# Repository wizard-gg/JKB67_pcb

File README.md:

# JKB67 RGB

[![CC BY-NC-SA 4.0][cc-by-nc-sa-shield]][cc-by-nc-sa]

## JKB65 RGB Hotswap PCB, compatible [Bakeneko65 V3](https://github.com/kkatano/bakeneko-65) Keyboard

---

## Front

## Back

---

[KiCAD PCB files](pcb/)

[Gerbers for PCB production](pcb/gerber/)

[QMK firmware](https://github.com/qmk/qmk_firmware/tree/master/keyboards/jadookb/jkb65)

[Fr4 Plate](https://github.com/desuko-mirai/Bakeneko-Screw-In-Stabilizer-Plates)

---

This work is licensed under a
[Creative Commons Attribution-NonCommercial-ShareAlike 4.0 International License][cc-by-nc-sa].

[![CC BY-NC-SA 4.0][cc-by-nc-sa-image]][cc-by-nc-sa]

[cc-by-nc-sa]: http://creativecommons.org/licenses/by-nc-sa/4.0/
[cc-by-nc-sa-image]: https://licensebuttons.net/l/by-nc-sa/4.0/88x31.png
[cc-by-nc-sa-shield]: https://img.shields.io/badge/License-CC%20BY--NC--SA%204.0-lightgrey.svg

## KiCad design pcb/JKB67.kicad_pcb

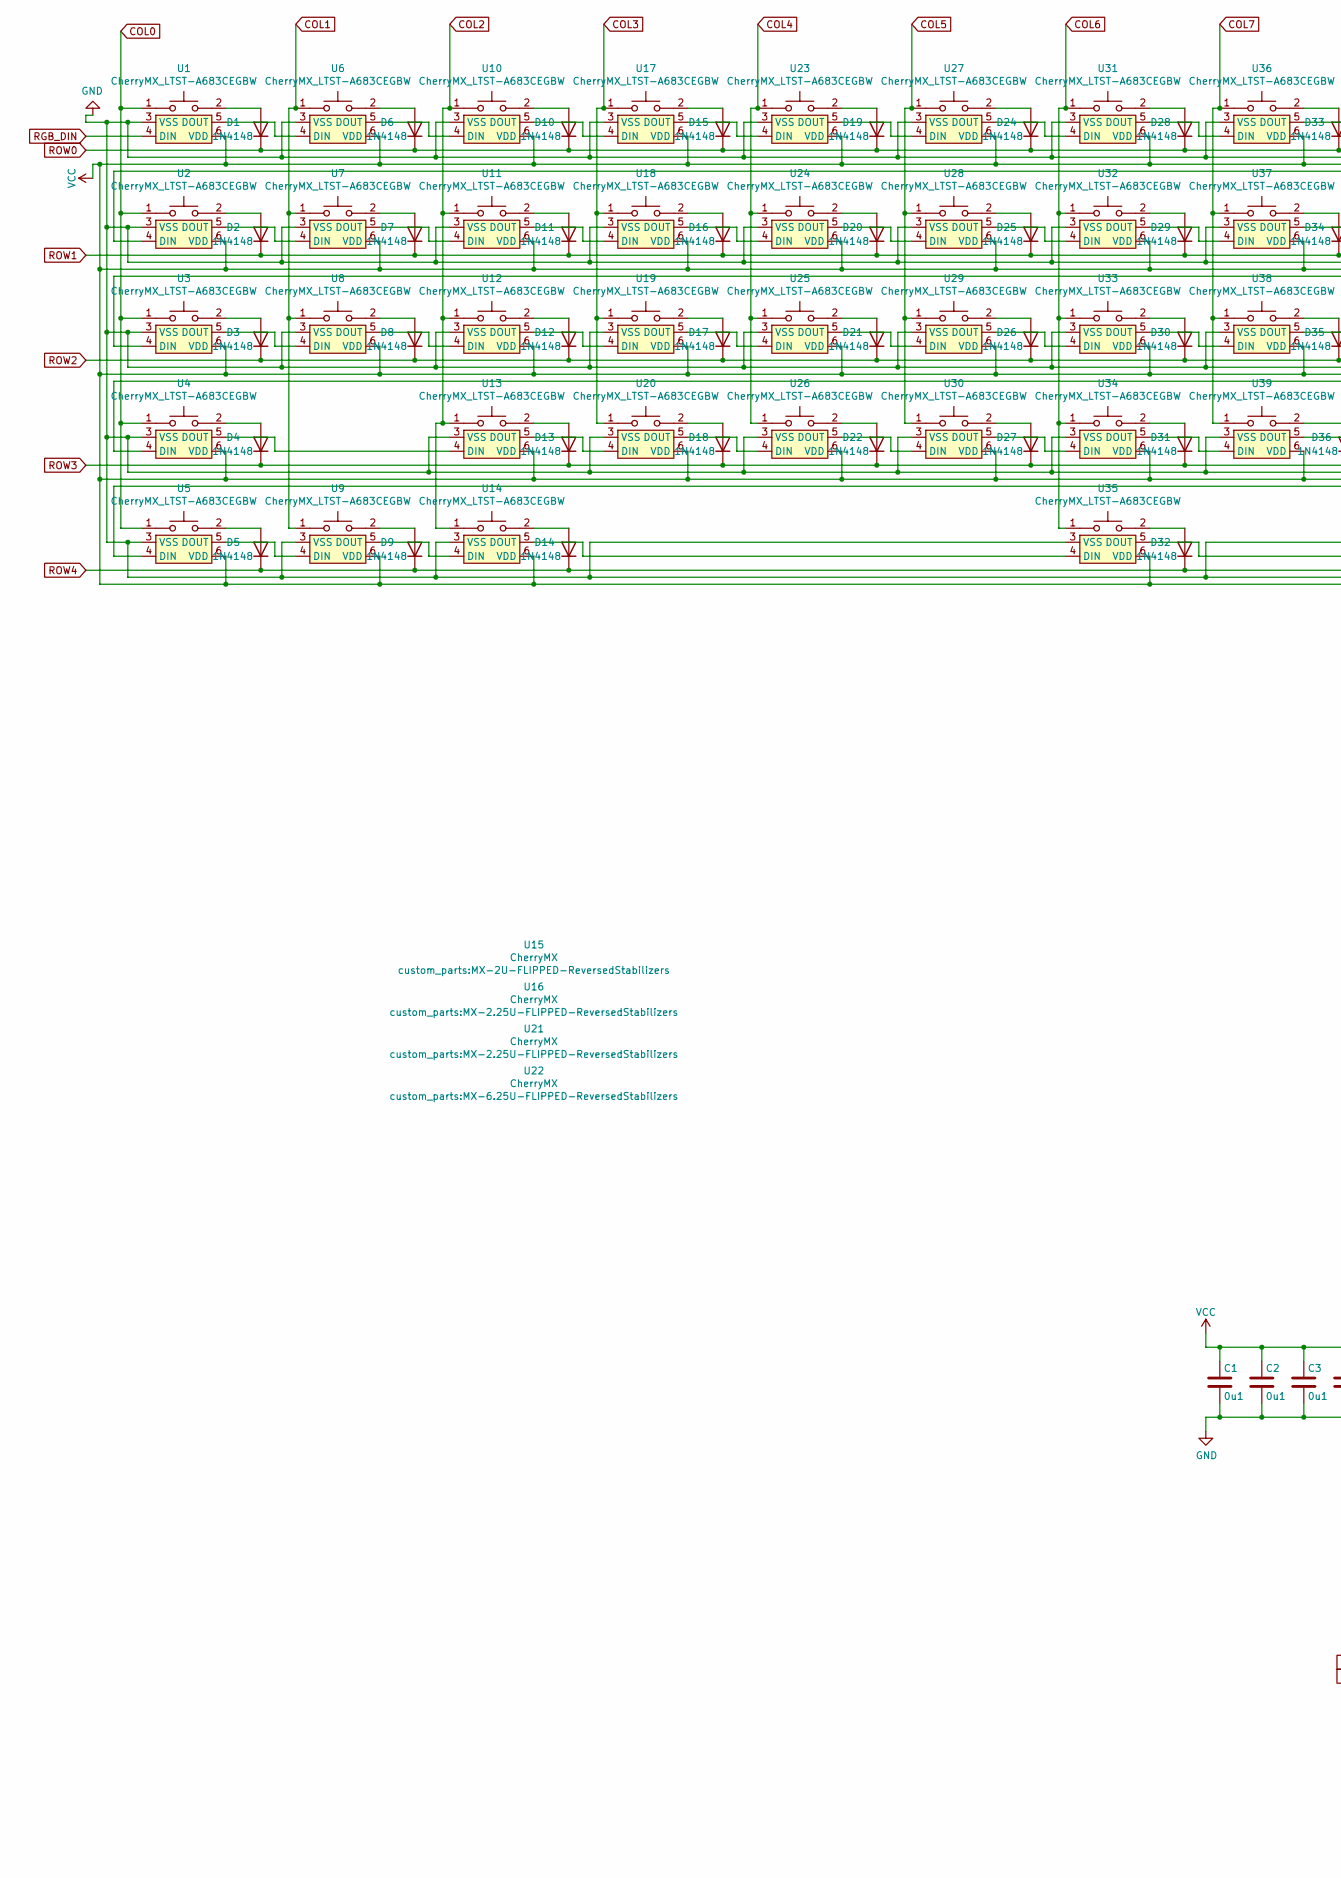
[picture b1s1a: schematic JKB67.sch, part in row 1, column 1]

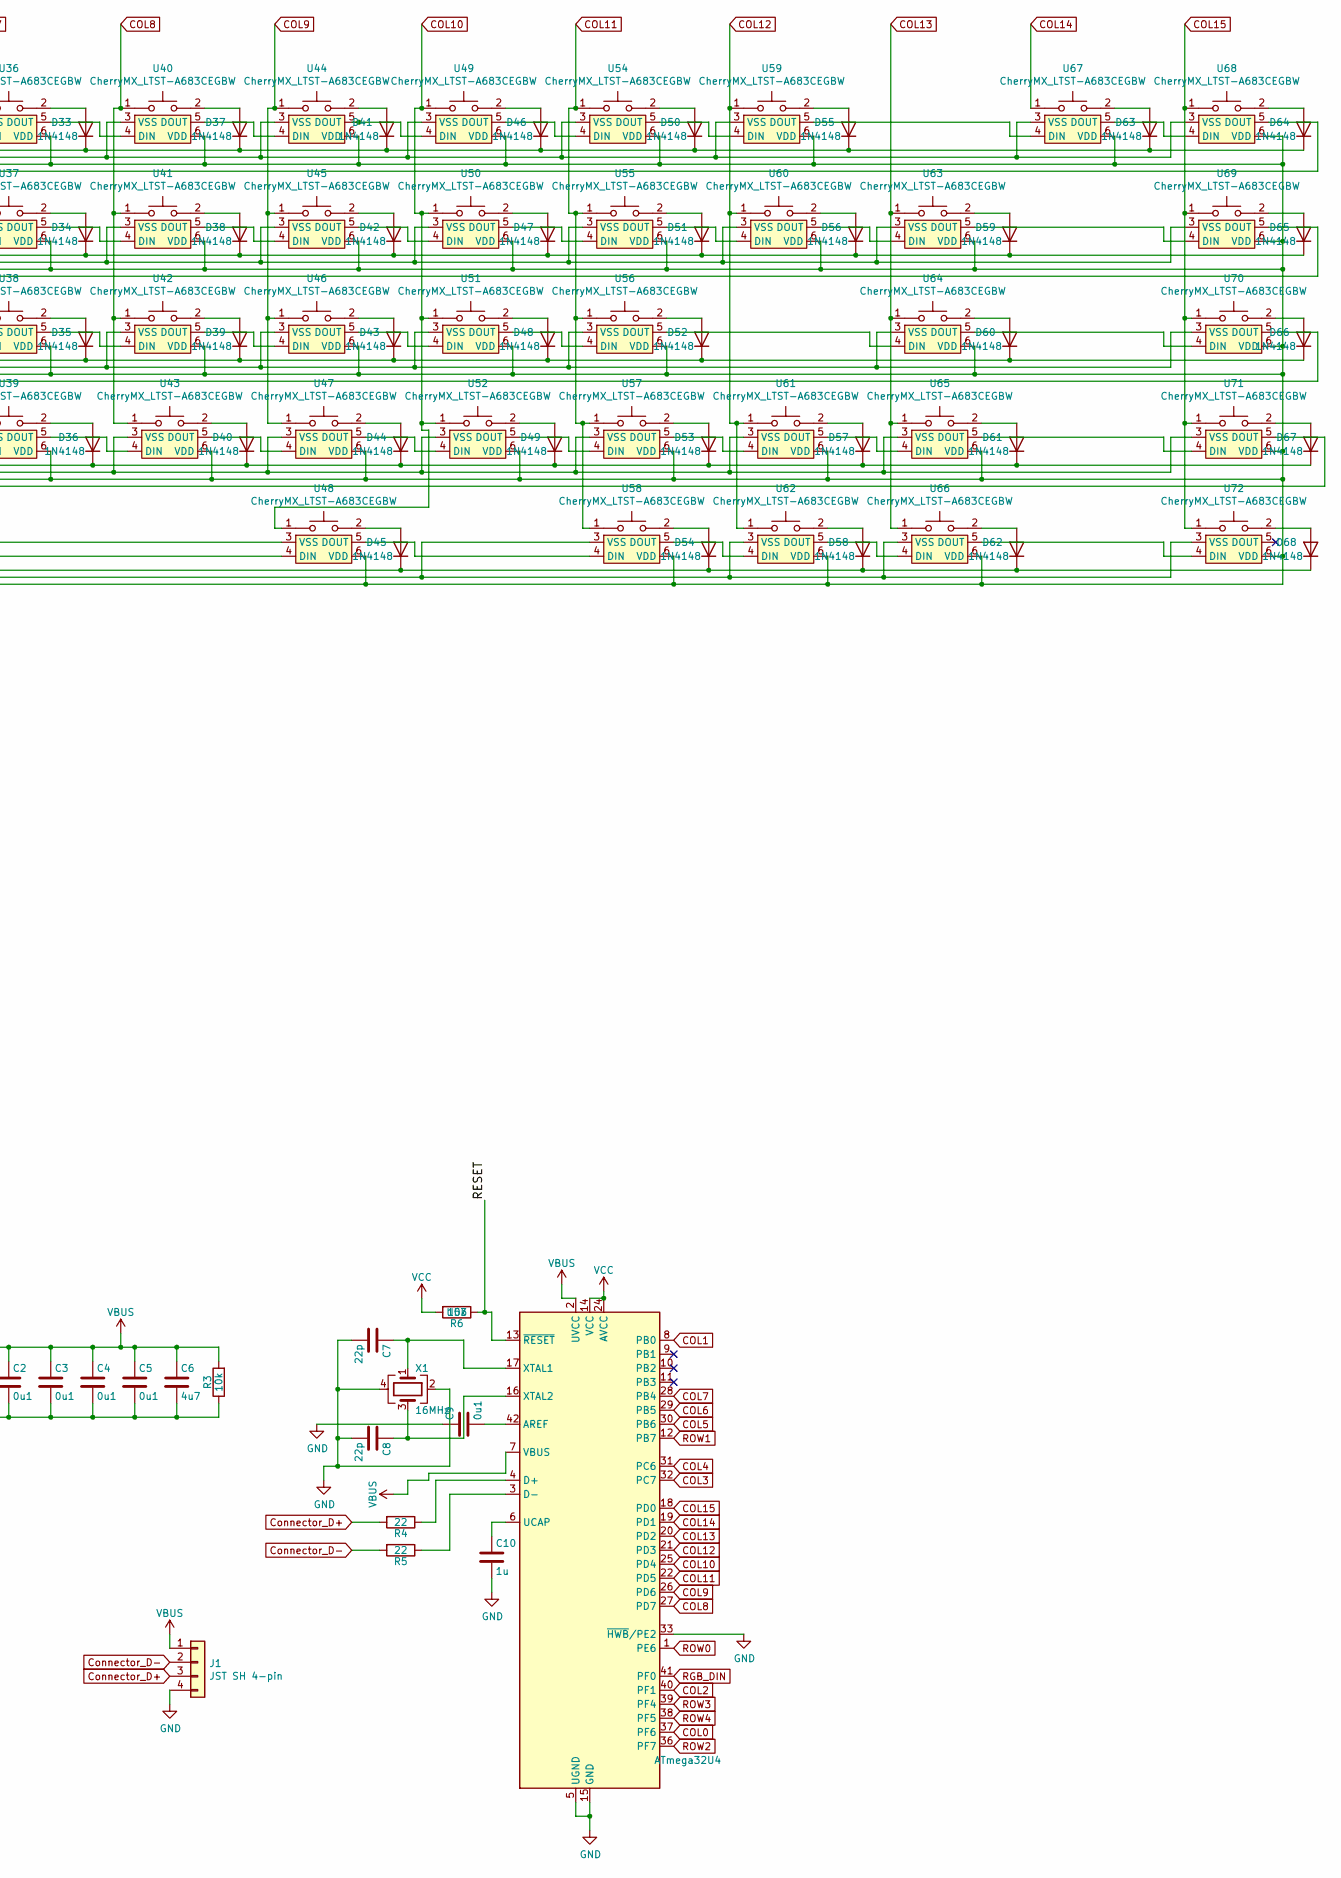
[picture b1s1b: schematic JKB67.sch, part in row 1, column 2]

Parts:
C1, C2, C3, C4, C5, C9: 0u1; C_0805_2012Metric_Pad1.18x1.45mm_HandSolder
C6: 4u7; C_0805_2012Metric_Pad1.18x1.45mm_HandSolder
C7, C8: 22p; C_0805_2012Metric_Pad1.18x1.45mm_HandSolder
C10: 1u; C_0805_2012Metric_Pad1.18x1.45mm_HandSolder
D1, D2, D3, D4, D5, D6, D7, D8, D9, D10, D11, D12, D13, D14, D15, D16, D17, D18, D19, D20, D21, D22, D24, D25, D26, D27, D28, D29, D30, D31, D32, D33, D34, D35, D36, D37, D38, D39, D40, D41, D42, D43, D44, D45, D46, D47, D48, D49, D50, D51, D52, D53, D54, D55, D56, D57, D58, D59, D60, D61, D62, D63, D64, D65, D66, D67, D68: 1N4148; D_SOD-123F; LCSC Part # C81598
J1: JST SH 4-pin; JST_SH_SM04B-SRSS-TB_04x1.25mm
R3, R6: 10k; R_0805_2012Metric_Pad1.20x1.40mm_HandSolder
R4, R5: 22; R_0805_2012Metric_Pad1.20x1.40mm_HandSolder
U1, U6, U7, U8, U10, U11, U12, U13, U17, U18, U19, U20, U23, U24, U25, U26, U27, U28, U29, U30, U31, U32, U33, U34, U36, U37, U38, U39, U40, U41, U42, U43, U44, U45, U46, U47, U49, U50, U51, U52, U54, U55, U56, U57, U59, U60, U62, U65, U66, U68, U69, U70, U71, U72: CherryMX_LTST-A683CEGBW; CherryMX_1.00u_5Pin_SK6812Mini
U2, U63: CherryMX_LTST-A683CEGBW; CherryMX_1.50u_5Pin_SK6812Mini
U3, U61: CherryMX_LTST-A683CEGBW; CherryMX_1.75u_5Pin_SK6812Mini
U4, U64: CherryMX_LTST-A683CEGBW; CherryMX_2.25u_5Pin_SK6812Mini
U5, U9, U14, U48, U58: CherryMX_LTST-A683CEGBW; CherryMX_1.25u_5Pin_SK6812Mini
U15: CherryMX; MX-2U-FLIPPED-ReversedStabilizers
U16, U21: CherryMX; MX-2.25U-FLIPPED-ReversedStabilizers
U22: CherryMX; MX-6.25U-FLIPPED-ReversedStabilizers
U35: CherryMX_LTST-A683CEGBW; CherryMX_6.25u_5Pin_SK6812Mini
U53: ATmega32U4; TQFP-44_10x10mm_P0.8mm
U67: CherryMX_LTST-A683CEGBW; CherryMX_2.00u_5Pin_SK6812Mini
X1: 16MHz; Crystal_SMD_SeikoEpson_FA238-4Pin_3.2x2.5mm

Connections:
/RESET: R6.1, U53.13 (~RESET)
COL0: U1.1, U2.1, U3.1, U4.1, U5.1, U53.37 (PF6)
COL1: U6.1, U7.1, U8.1, U9.1, U53.8 (PB0)
COL2: U10.1, U11.1, U12.1, U13.1, U14.1, U53.40 (PF1)
COL3: U17.1, U18.1, U19.1, U20.1, U53.32 (PC7)
COL4: U23.1, U24.1, U25.1, U26.1, U53.31 (PC6)
COL5: U27.1, U28.1, U29.1, U30.1, U53.30 (PB6)
COL6: U31.1, U32.1, U33.1, U34.1, U35.1, U53.29 (PB5)
COL7: U36.1, U37.1, U38.1, U39.1, U53.28 (PB4)
COL8: U40.1, U41.1, U42.1, U43.1, U53.27 (PD7)
COL9: U44.1, U45.1, U46.1, U47.1, U53.26 (PD6)
COL10: U48.1, U49.1, U50.1, U51.1, U52.1, U53.25 (PD4)
COL11: U53.22 (PD5), U54.1, U55.1, U56.1, U57.1, U58.1
COL12: U53.21 (PD3), U59.1, U60.1, U61.1, U62.1
COL13: U53.20 (PD2), U63.1, U64.1, U65.1, U66.1
COL14: U53.19 (PD1), U67.1
COL15: U53.18 (PD0), U68.1, U69.1, U70.1, U71.1, U72.1
Connector_D+: J1.3, R4.2
Connector_D-: J1.2, R5.2
GND: C1.2, C2.2, C3.2, C4.2, C5.2, C6.2, C7.2, C8.2, C9.1, C10.2, J1.4, R3.1, U1.3 (VSS), U2.3 (VSS), U3.3 (VSS), U4.3 (VSS), U5.3 (VSS), U6.3 (VSS), U7.3 (VSS), U8.3 (VSS), U9.3 (VSS), U10.3 (VSS), U11.3 (VSS), U12.3 (VSS), U13.3 (VSS), U14.3 (VSS), U17.3 (VSS), U18.3 (VSS), U19.3 (VSS), U20.3 (VSS), U23.3 (VSS), U24.3 (VSS), U25.3 (VSS), U26.3 (VSS), U27.3 (VSS), U28.3 (VSS), U29.3 (VSS), U30.3 (VSS), U31.3 (VSS), U32.3 (VSS), U33.3 (VSS), U34.3 (VSS), U35.3 (VSS), U36.3 (VSS), U37.3 (VSS), U38.3 (VSS), U39.3 (VSS), U40.3 (VSS), U41.3 (VSS), U42.3 (VSS), U43.3 (VSS), U44.3 (VSS), U45.3 (VSS), U46.3 (VSS), U47.3 (VSS), U48.3 (VSS), U49.3 (VSS), U50.3 (VSS), U51.3 (VSS), U52.3 (VSS), U53.5 (UGND), U53.15 (GND), U53.23 (GND), U53.33 (~HWB~/PE2), U53.35 (GND), U53.43 (GND), U54.3 (VSS), U55.3 (VSS), U56.3 (VSS), U57.3 (VSS), U58.3 (VSS), U59.3 (VSS), U60.3 (VSS), U61.3 (VSS), U62.3 (VSS), U63.3 (VSS), U64.3 (VSS), U65.3 (VSS), U66.3 (VSS), U67.3 (VSS), U68.3 (VSS), U69.3 (VSS), U70.3 (VSS), U71.3 (VSS), U72.3 (VSS), X1.2, X1.4
unnamed: C7.1, U53.17 (XTAL1), X1.1
unnamed: C8.1, U53.16 (XTAL2), X1.3
unnamed: C9.2, U53.42 (AREF)
unnamed: C10.1, U53.6 (UCAP)
unnamed: D1.2 (A), U1.2
unnamed: D2.2 (A), U2.2
unnamed: D3.2 (A), U3.2
unnamed: D4.2 (A), U4.2
unnamed: D5.2 (A), U5.2
unnamed: D6.2 (A), U6.2
unnamed: D7.2 (A), U7.2
unnamed: D8.2 (A), U8.2
unnamed: D9.2 (A), U9.2
unnamed: D10.2 (A), U10.2
unnamed: D11.2 (A), U11.2
unnamed: D12.2 (A), U12.2
unnamed: D13.2 (A), U13.2
unnamed: D14.2 (A), U14.2
unnamed: D15.2 (A), U17.2
unnamed: D16.2 (A), U18.2
unnamed: D17.2 (A), U19.2
unnamed: D18.2 (A), U20.2
unnamed: D19.2 (A), U23.2
unnamed: D20.2 (A), U24.2
unnamed: D21.2 (A), U25.2
unnamed: D22.2 (A), U26.2
unnamed: D24.2 (A), U27.2
unnamed: D25.2 (A), U28.2
unnamed: D26.2 (A), U29.2
unnamed: D27.2 (A), U30.2
unnamed: D28.2 (A), U31.2
unnamed: D29.2 (A), U32.2
unnamed: D30.2 (A), U33.2
unnamed: D31.2 (A), U34.2
unnamed: D32.2 (A), U35.2
unnamed: D33.2 (A), U36.2
unnamed: D34.2 (A), U37.2
unnamed: D35.2 (A), U38.2
unnamed: D36.2 (A), U39.2
unnamed: D37.2 (A), U40.2
unnamed: D38.2 (A), U41.2
unnamed: D39.2 (A), U42.2
unnamed: D40.2 (A), U43.2
unnamed: D41.2 (A), U44.2
unnamed: D42.2 (A), U45.2
unnamed: D43.2 (A), U46.2
unnamed: D44.2 (A), U47.2
unnamed: D45.2 (A), U48.2
unnamed: D46.2 (A), U49.2
unnamed: D47.2 (A), U50.2
unnamed: D48.2 (A), U51.2
unnamed: D49.2 (A), U52.2
unnamed: D50.2 (A), U54.2
unnamed: D51.2 (A), U55.2
unnamed: D52.2 (A), U56.2
unnamed: D53.2 (A), U57.2
unnamed: D54.2 (A), U58.2
unnamed: D55.2 (A), U59.2
unnamed: D56.2 (A), U60.2
unnamed: D57.2 (A), U61.2
unnamed: D58.2 (A), U62.2
unnamed: D59.2 (A), U63.2
unnamed: D60.2 (A), U64.2
unnamed: D61.2 (A), U65.2
unnamed: D62.2 (A), U66.2
unnamed: D63.2 (A), U67.2
unnamed: D64.2 (A), U68.2
unnamed: D65.2 (A), U69.2
unnamed: D66.2 (A), U70.2
unnamed: D67.2 (A), U71.2
unnamed: D68.2 (A), U72.2
unnamed: R4.1, U53.4 (D+)
unnamed: R5.1, U53.3 (D-)
unnamed: U1.5 (DOUT), U6.4 (DIN)
unnamed: U2.4 (DIN), U68.5 (DOUT)
unnamed: U2.5 (DOUT), U7.4 (DIN)
unnamed: U3.4 (DIN), U69.5 (DOUT)
unnamed: U3.5 (DOUT), U8.4 (DIN)
unnamed: U4.4 (DIN), U70.5 (DOUT)
unnamed: U5.4 (DIN), U71.5 (DOUT)
unnamed: U5.5 (DOUT), U9.4 (DIN)
unnamed: U6.5 (DOUT), U10.4 (DIN)
unnamed: U10.5 (DOUT), U17.4 (DIN)
unnamed: U7.5 (DOUT), U11.4 (DIN)
unnamed: U11.5 (DOUT), U18.4 (DIN)
unnamed: U8.5 (DOUT), U12.4 (DIN)
unnamed: U12.5 (DOUT), U19.4 (DIN)
unnamed: U4.5 (DOUT), U13.4 (DIN)
unnamed: U13.5 (DOUT), U20.4 (DIN)
unnamed: U9.5 (DOUT), U14.4 (DIN)
unnamed: U14.5 (DOUT), U35.4 (DIN)
unnamed: U17.5 (DOUT), U23.4 (DIN)
unnamed: U18.5 (DOUT), U24.4 (DIN)
unnamed: U19.5 (DOUT), U25.4 (DIN)
unnamed: U20.5 (DOUT), U26.4 (DIN)
unnamed: U23.5 (DOUT), U27.4 (DIN)
unnamed: U24.5 (DOUT), U28.4 (DIN)
unnamed: U25.5 (DOUT), U29.4 (DIN)
unnamed: U26.5 (DOUT), U30.4 (DIN)
unnamed: U27.5 (DOUT), U31.4 (DIN)
unnamed: U28.5 (DOUT), U32.4 (DIN)
unnamed: U29.5 (DOUT), U33.4 (DIN)
unnamed: U30.5 (DOUT), U34.4 (DIN)
unnamed: U31.5 (DOUT), U36.4 (DIN)
unnamed: U32.5 (DOUT), U37.4 (DIN)
unnamed: U33.5 (DOUT), U38.4 (DIN)
unnamed: U34.5 (DOUT), U39.4 (DIN)
unnamed: U35.5 (DOUT), U48.4 (DIN)
unnamed: U36.5 (DOUT), U40.4 (DIN)
unnamed: U37.5 (DOUT), U41.4 (DIN)
unnamed: U38.5 (DOUT), U42.4 (DIN)
unnamed: U39.5 (DOUT), U43.4 (DIN)
unnamed: U40.5 (DOUT), U44.4 (DIN)
unnamed: U41.5 (DOUT), U45.4 (DIN)
unnamed: U42.5 (DOUT), U46.4 (DIN)
unnamed: U43.5 (DOUT), U47.4 (DIN)
unnamed: U44.5 (DOUT), U49.4 (DIN)
unnamed: U45.5 (DOUT), U50.4 (DIN)
unnamed: U46.5 (DOUT), U51.4 (DIN)
unnamed: U47.5 (DOUT), U52.4 (DIN)
unnamed: U48.5 (DOUT), U58.4 (DIN)
unnamed: U49.5 (DOUT), U54.4 (DIN)
unnamed: U50.5 (DOUT), U55.4 (DIN)
unnamed: U51.5 (DOUT), U56.4 (DIN)
unnamed: U52.5 (DOUT), U57.4 (DIN)
unnamed: U54.5 (DOUT), U59.4 (DIN)
unnamed: U55.5 (DOUT), U60.4 (DIN)
unnamed: U56.5 (DOUT), U64.4 (DIN)
unnamed: U57.5 (DOUT), U61.4 (DIN)
unnamed: U58.5 (DOUT), U62.4 (DIN)
unnamed: U59.5 (DOUT), U67.4 (DIN)
unnamed: U60.5 (DOUT), U63.4 (DIN)
unnamed: U61.5 (DOUT), U65.4 (DIN)
unnamed: U62.5 (DOUT), U66.4 (DIN)
unnamed: U63.5 (DOUT), U69.4 (DIN)
unnamed: U64.5 (DOUT), U70.4 (DIN)
unnamed: U65.5 (DOUT), U71.4 (DIN)
unnamed: U66.5 (DOUT), U72.4 (DIN)
unnamed: U67.5 (DOUT), U68.4 (DIN)
RGB_DIN: U1.4 (DIN), U53.41 (PF0)
ROW0: D1.1 (K), D6.1 (K), D10.1 (K), D15.1 (K), D19.1 (K), D24.1 (K), D28.1 (K), D33.1 (K), D37.1 (K), D41.1 (K), D46.1 (K), D50.1 (K), D55.1 (K), D63.1 (K), D64.1 (K), U53.1 (PE6)
ROW1: D2.1 (K), D7.1 (K), D11.1 (K), D16.1 (K), D20.1 (K), D25.1 (K), D29.1 (K), D34.1 (K), D38.1 (K), D42.1 (K), D47.1 (K), D51.1 (K), D56.1 (K), D59.1 (K), D65.1 (K), U53.12 (PB7)
ROW2: D3.1 (K), D8.1 (K), D12.1 (K), D17.1 (K), D21.1 (K), D26.1 (K), D30.1 (K), D35.1 (K), D39.1 (K), D43.1 (K), D48.1 (K), D52.1 (K), D60.1 (K), D66.1 (K), U53.36 (PF7)
ROW3: D4.1 (K), D13.1 (K), D18.1 (K), D22.1 (K), D27.1 (K), D31.1 (K), D36.1 (K), D40.1 (K), D44.1 (K), D49.1 (K), D53.1 (K), D57.1 (K), D61.1 (K), D67.1 (K), U53.39 (PF4)
ROW4: D5.1 (K), D9.1 (K), D14.1 (K), D32.1 (K), D45.1 (K), D54.1 (K), D58.1 (K), D62.1 (K), D68.1 (K), U53.38 (PF5)
VBUS: C1.1, C2.1, C3.1, C4.1, C5.1, C6.1, J1.1, R3.2, R6.2, U1.6 (VDD), U2.6 (VDD), U3.6 (VDD), U4.6 (VDD), U5.6 (VDD), U6.6 (VDD), U7.6 (VDD), U8.6 (VDD), U9.6 (VDD), U10.6 (VDD), U11.6 (VDD), U12.6 (VDD), U13.6 (VDD), U14.6 (VDD), U17.6 (VDD), U18.6 (VDD), U19.6 (VDD), U20.6 (VDD), U23.6 (VDD), U24.6 (VDD), U25.6 (VDD), U26.6 (VDD), U27.6 (VDD), U28.6 (VDD), U29.6 (VDD), U30.6 (VDD), U31.6 (VDD), U32.6 (VDD), U33.6 (VDD), U34.6 (VDD), U35.6 (VDD), U36.6 (VDD), U37.6 (VDD), U38.6 (VDD), U39.6 (VDD), U40.6 (VDD), U41.6 (VDD), U42.6 (VDD), U43.6 (VDD), U44.6 (VDD), U45.6 (VDD), U46.6 (VDD), U47.6 (VDD), U48.6 (VDD), U49.6 (VDD), U50.6 (VDD), U51.6 (VDD), U52.6 (VDD), U53.2 (UVCC), U53.7 (VBUS), U53.14 (VCC), U53.24 (AVCC), U53.34 (VCC), U53.44 (AVCC), U54.6 (VDD), U55.6 (VDD), U56.6 (VDD), U57.6 (VDD), U58.6 (VDD), U59.6 (VDD), U60.6 (VDD), U61.6 (VDD), U62.6 (VDD), U63.6 (VDD), U64.6 (VDD), U65.6 (VDD), U66.6 (VDD), U67.6 (VDD), U68.6 (VDD), U69.6 (VDD), U70.6 (VDD), U71.6 (VDD), U72.6 (VDD)

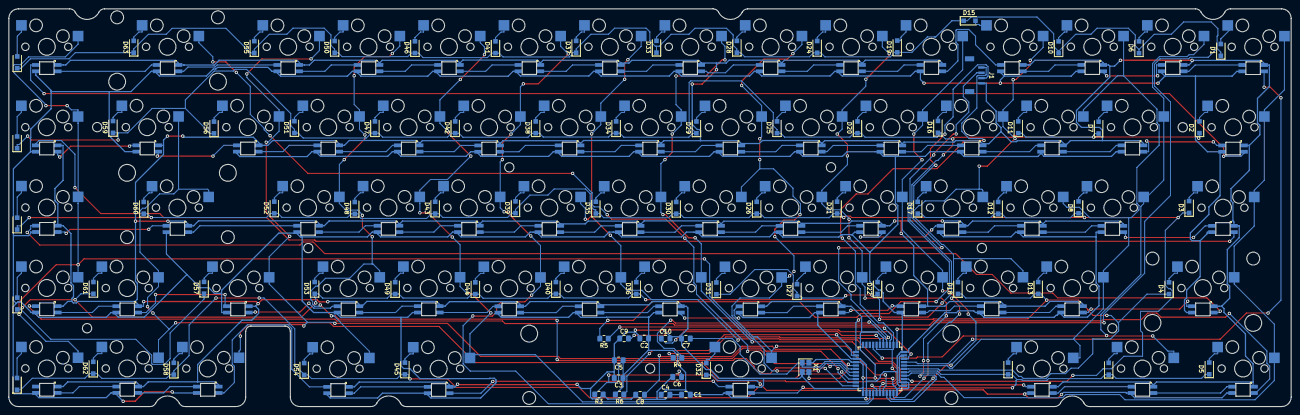
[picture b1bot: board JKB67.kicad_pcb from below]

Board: 2 copper layers, 303.8 x 94.2 mm, 157 parts (84 on the bottom side), 166 nets.

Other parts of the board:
G1: LOGO; qmk_logo
G2: LOGO; vial_logo
